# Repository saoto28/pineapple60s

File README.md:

# pineapple60s
Custom keyboard for ThinkPad X13 Gen2

## folder

### [/KiCAD8][1]
[1]:/KiCAD8

- PCB CAD files

### [/qmk_firmware][2]
[2]:/qmk_firmware/keyboards/pineapple/p60s

- keyboard configuration of qmk_firware 

Full qmk_firmware repository is here.
https://github.com/saoto28/qmk_firmware/tree/pineapple

## How to modify ThinkPad X13 Gen2 (Japanese)
https://note.com/saoto28/n/n716b7ca2e1f9

## links
All Pineapple projects repository:
https://github.com/saoto28/pineapple60

Twitter: https://x.com/saoto28

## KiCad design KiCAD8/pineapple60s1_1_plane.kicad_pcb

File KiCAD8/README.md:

# Pineapple60s PCB design
## prerequisite
CAD: KiCAD 8

## history
### pineapple60s1_1_plane.* : remove key layouts from ver.1.1

### (pineapple60s1_1.* : ver.1.1, fixed some manual corrections made when installing ver. 1.0 at 2025-06)

### pineapple60s1_0a.* : same as ver 1.0, but, changed library folder location at 2025-06

[pineapple60s ver.1.0a schematic](images_and_pdf/pineapple60s1_0a_sch.pdf)

### (pineapple60s1_0.* : pineapple60s ver.1.0 first produced at 2025-05)

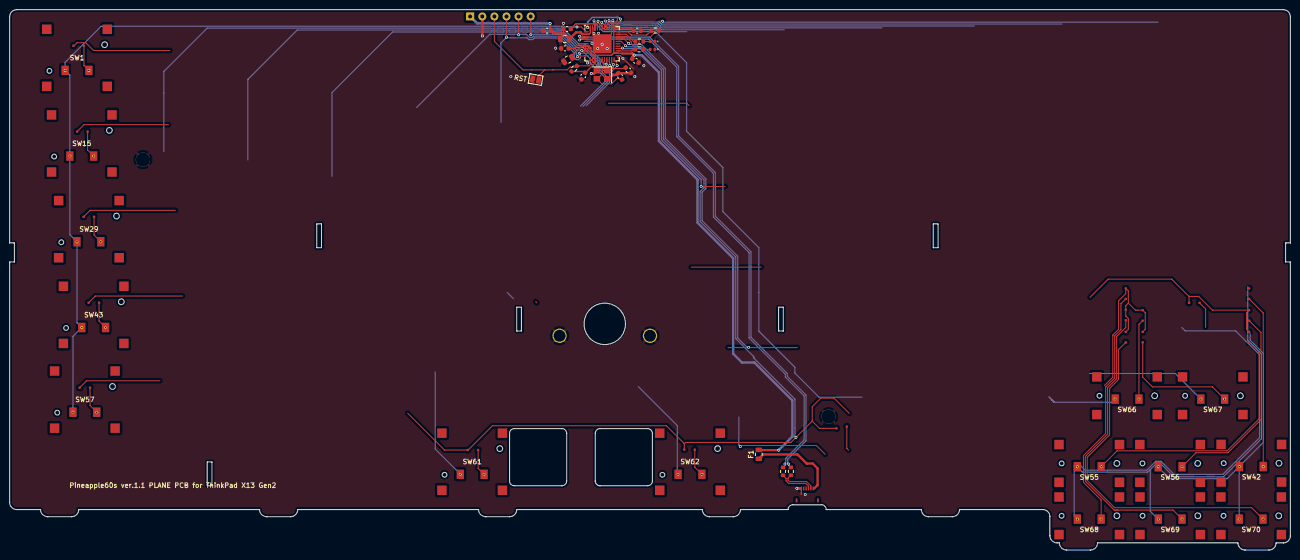
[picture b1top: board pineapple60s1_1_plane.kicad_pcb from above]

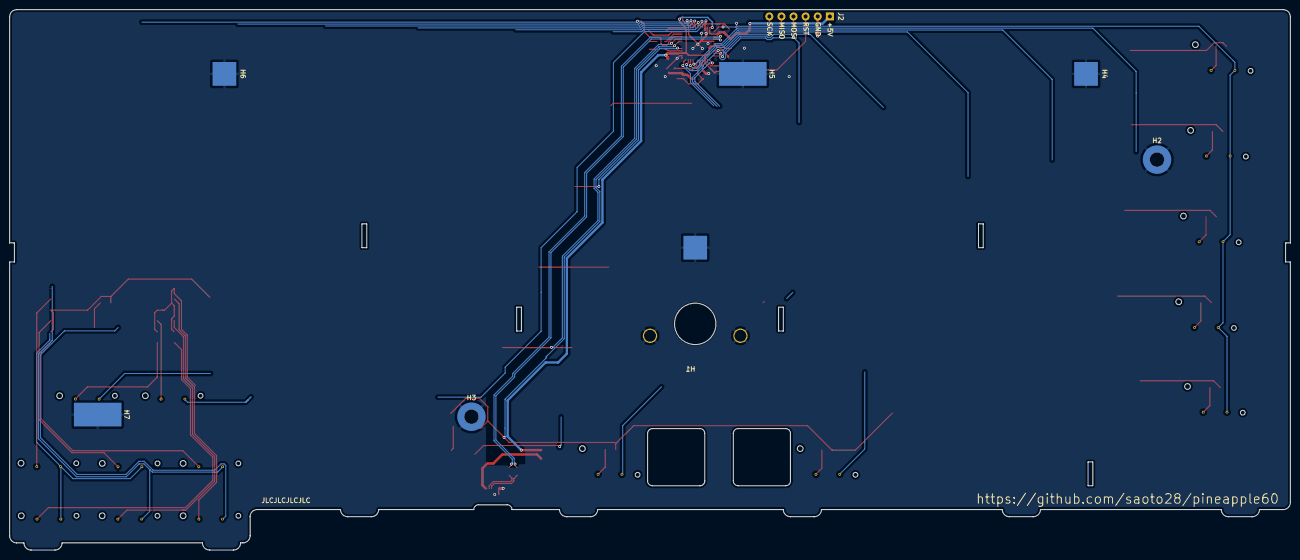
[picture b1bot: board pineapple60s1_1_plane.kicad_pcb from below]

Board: 2 copper layers, 268.9 x 113.4 mm, 63 parts (7 on the bottom side), 46 nets.

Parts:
C1, C2, C3, C4: 0.1u; C_0603_1608Metric
C5: 4.7u; C_0805_2012Metric
C6: 10u; C_0805_2012Metric
C7, C8: 1u; C_0603_1608Metric
C9, C10: 22pF; C_0603_1608Metric
D1, D15, D29, D42, D43, D54, D55, D56, D57, D61, D62, D63, D66, D67, D68, D69, D70: 1N4148WS; D_SOD-323F_mod
D71, D72: LED; LED_0402_1005Metric
F1: SMD0805-020; Fuse_0805_2012Metric
H1: Trackpoint_X13G2
H2, H3: MountingHole; MountingHole_3mm_Pad_Top_noVia
H4, H6: MountingHole_Pad_MP; SolderWirePad_1x01_SMD_5x5mm
H5, H7: MountingHole_Pad_MP; SolderWirePad_1x01_SMD_5x10mm
J1: to PC; HRS_FH34SRJ-6S-0.5SH_50_mod
J2: boot; PinHeader_0.8x06_P2.54mm_Vertical_noline_toponly
R1, R6: 10k; R_0603_1608Metric
R2, R3: 2.2k; R_0603_1608Metric
R4, R5: 22; R_0603_1608Metric
SW1, SW15, SW29, SW43: SW_Push; CPG1316S01D02_1.25U
SW42, SW55, SW56, SW66, SW67, SW68, SW69, SW70: SW_Push; CPG1316M01D02_0.5U
SW57: SW_Push; CPG1316S01D02_1U
SW61, SW62: SW_Push; CPG1316S01D02_2U
SW71: RST; SolderJumper-2_P1.3mm_Open_Pad1.0x1.5mm
U1: ATmega32U4-M; QFN-44-1EP_7x7mm_P0.5mm_EP5.2x5.2mm
Y1: 16MHz SMD crystal oscillator 18pF; Crystal_SMD_3225-4Pin_3.2x2.5mm

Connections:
+5V: C1.2, C2.2, C3.2, C4.2, C5.2, C6.2, F1.2, J2.1, R6.2, U1.2 (UVCC), U1.7 (VBUS), U1.14 (VCC), U1.24 (AVCC), U1.34 (VCC), U1.44 (AVCC)
/DM: J1.2, R5.1
/DP: J1.3, R4.1
/MISO: J2.5, SW61.1, U1.11 (PB3)
/MOSI: J2.4, SW62.1, U1.10 (PB2)
/RST: J2.3, R6.1, SW71.1, U1.13 (~RESET)
/SCK: J2.6, U1.9 (PB1)
/col0: SW1.1, SW15.1, SW29.1, SW43.1, SW57.1, U1.1 (PE6)
/col9: SW66.1, U1.39 (PF4)
/col10: SW67.1, U1.38 (PF5)
/col11: SW68.1, U1.37 (PF6)
/col12: SW55.1, SW69.1, U1.36 (PF7)
/col13: SW42.1, SW56.1, SW70.1, U1.31 (PC6)
/row0: D1.1 (K), U1.22 (PD5)
/row1: D15.1 (K), U1.26 (PD6)
/row2: D29.1 (K), D42.1 (K), U1.12 (PB7)
/row3: D43.1 (K), D54.1 (K), D55.1 (K), D56.1 (K), U1.30 (PB6)
/row4: D57.1 (K), D61.1 (K), D62.1 (K), D63.1 (K), D66.1 (K), D67.1 (K), D68.1 (K), D69.1 (K), D70.1 (K), U1.29 (PB5)
GND: C1.1, C2.1, C3.1, C4.1, C5.1, C6.1, C7.1, C8.1, C9.1, C10.1, D71.1 (K), D72.1 (K), H1.1 (GND), H1.2 (GND), H1.3 (GND), H2.1, H3.1, H4.1, H5.1, H6.1, H7.1, J1.6, J2.2, R1.1, SW71.2, U1.5 (UGND), U1.15 (GND), U1.23 (GND), U1.35 (GND), U1.43 (GND), U1.45 (GND), Y1.2, Y1.4
unnamed: D1.2 (A), SW1.2
unnamed: D15.2 (A), SW15.2
unnamed: D29.2 (A), SW29.2
unnamed: D42.2 (A), SW42.2
unnamed: D43.2 (A), SW43.2
unnamed: D55.2 (A), SW55.2
unnamed: D56.2 (A), SW56.2
unnamed: D57.2 (A), SW57.2
unnamed: D61.2 (A), SW61.2
unnamed: D62.2 (A), SW62.2
unnamed: D66.2 (A), SW66.2
unnamed: D67.2 (A), SW67.2
unnamed: D68.2 (A), SW68.2
unnamed: D69.2 (A), SW69.2
unnamed: D70.2 (A), SW70.2
unnamed: D71.2 (A), R2.1
unnamed: D72.2 (A), R3.1
unnamed: F1.1, J1.1
unnamed: C7.2, U1.42 (AREF)
unnamed: R4.2, U1.4 (D+)
unnamed: R5.2, U1.3 (D-)
unnamed: R3.2, U1.32 (PC7)
unnamed: R2.2, U1.25 (PD4)
unnamed: C8.2, U1.6 (UCAP)
unnamed: C9.2, U1.17 (XTAL1), Y1.1
unnamed: C10.2, U1.16 (XTAL2), Y1.3
unnamed: R1.2, U1.33 (~HWB/PE2)

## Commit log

2025-06-08 add kicad_sch
2025-06-08 edit README.md
2025-06-08 del pineapple60.kicad_sch
2025-06-08 edit README.md and move images
2025-06-08 add a pic on README.md of the root
2025-06-08 add a pic
2025-06-09 add link in README.md
